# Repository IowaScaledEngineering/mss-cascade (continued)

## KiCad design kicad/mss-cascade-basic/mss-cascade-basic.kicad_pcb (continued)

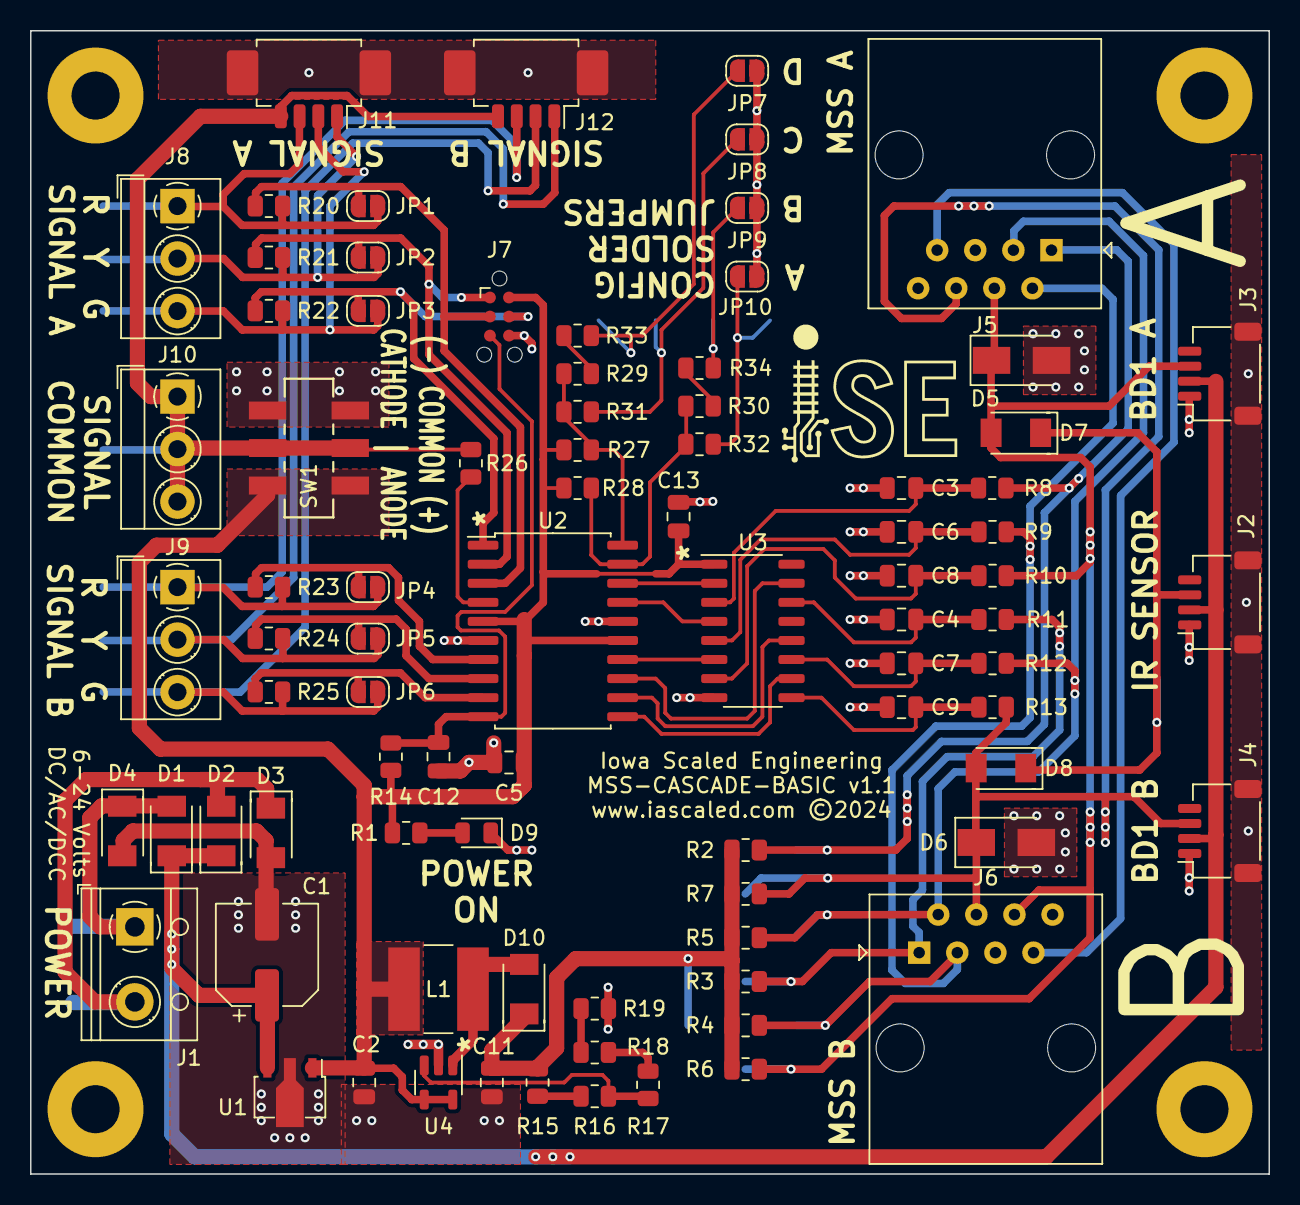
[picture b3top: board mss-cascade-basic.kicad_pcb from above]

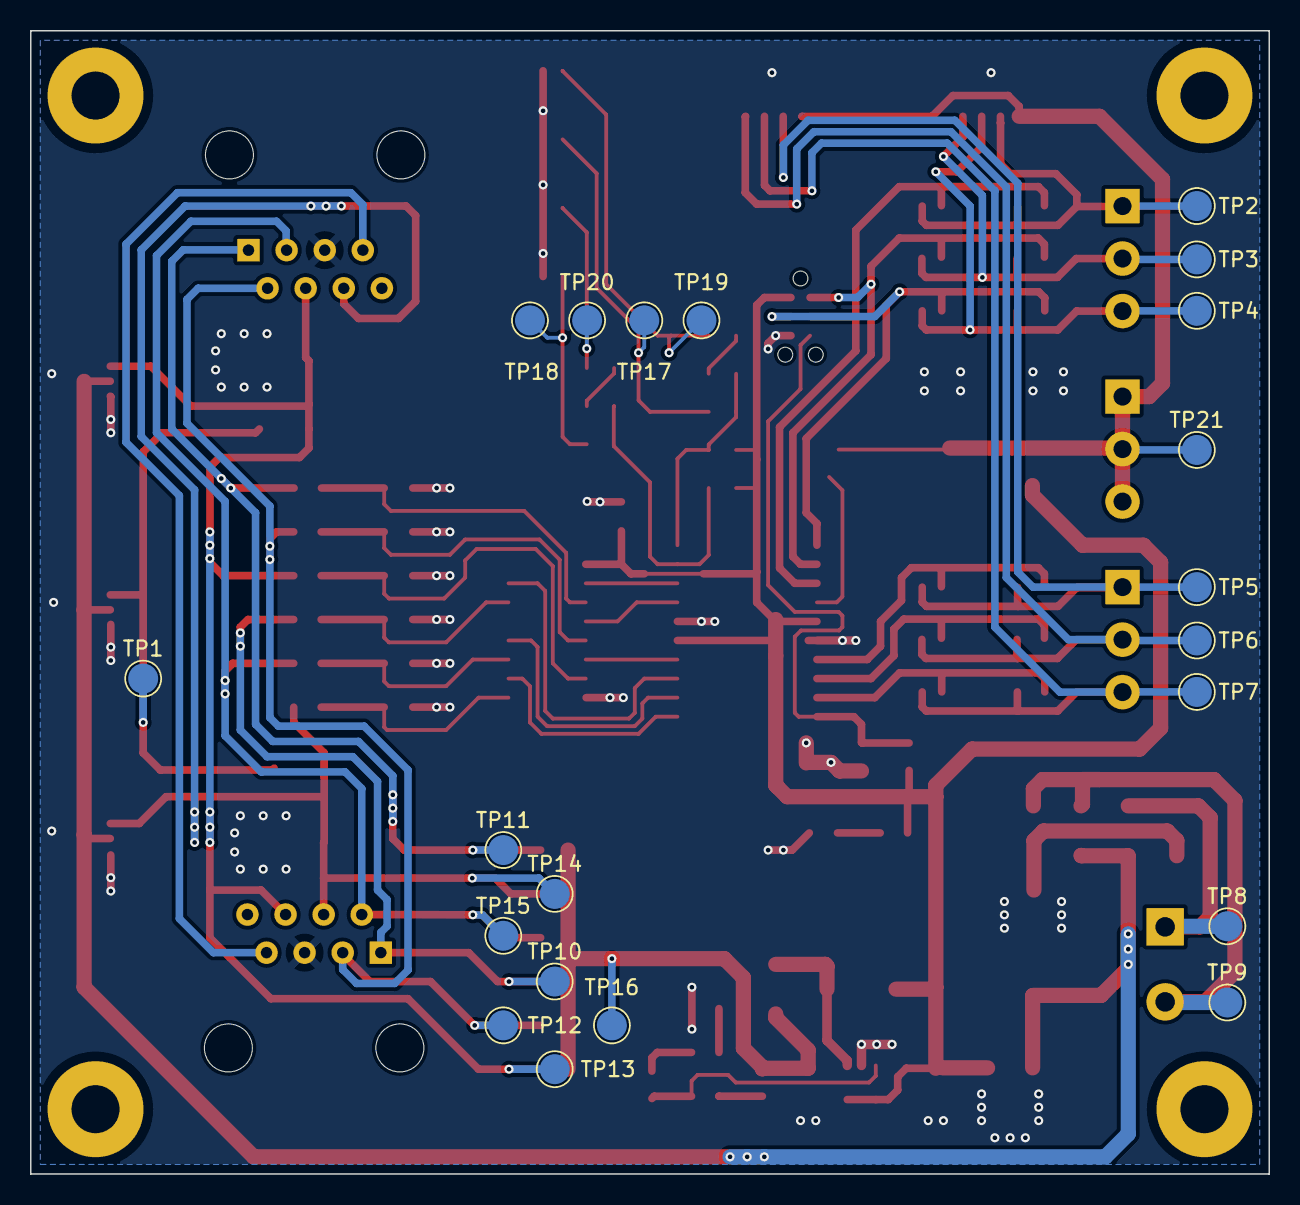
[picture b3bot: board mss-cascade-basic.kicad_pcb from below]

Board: 2 copper layers, 82.6 x 76.2 mm, 109 parts (21 on the bottom side), 55 nets.

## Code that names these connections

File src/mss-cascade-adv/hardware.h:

/*************************************************************************
Title:    Hardware Configuration for MSS-SIDING
Authors:  Michael Petersen <railfan@drgw.net>
          Nathan D. Holmes <maverick@drgw.net>
File:     $Id: $
License:  GNU General Public License v3

LICENSE:
    Copyright (C) 2024 Michael Petersen & Nathan Holmes

    This program is free software; you can redistribute it and/or modify
    it under the terms of the GNU General Public License as published by
    the Free Software Foundation; either version 3 of the License, or
    any later version.

    This program is distributed in the hope that it will be useful,
    but WITHOUT ANY WARRANTY; without even the implied warranty of
    MERCHANTABILITY or FITNESS FOR A PARTICULAR PURPOSE.  See the
    GNU General Public License for more details.

*************************************************************************/

#ifndef _HARDWARE_H_
#define _HARDWARE_H_

#define SWITCH_UPDATE_TIME_MS     25
#define LOOP_UPDATE_TIME_MS       50
#define TURNOUT_LOCKOUT_TIME_MS  200
#define STARTUP_LOCKOUT_TIME_MS  500

#define EEPROM_SIGNAL_AU_BASE  ((uint8_t*)0x00)
#define EEPROM_SIGNAL_AL_BASE  ((uint8_t*)0x08)
#define EEPROM_SIGNAL_BU_BASE  ((uint8_t*)0x10)
#define EEPROM_SIGNAL_BL_BASE  ((uint8_t*)0x18)


#define TCA9555_ADDR_000  0x20
#define TCA9555_ADDR_001  0x21
#define TCA9555_GPIN0        0
#define TCA9555_GPIN1        1
#define TCA9555_GPOUT0       2
#define TCA9555_GPOUT1       3
#define TCA9555_GPDDR0       6
#define TCA9555_GPDDR1       7

// TCA9555 0x20 - GPIO 0
//  IO07 - Input  - Option Switch E
//  IO06 - Input  - Option Switch D
//  IO05 - Input  - Option Switch C
//  IO04 - Input  - Option Switch B
//  IO03 - Input  - Option Switch A
//  IO02 - Input  - /SW3
//  IO01 - Input  - /SW4
//  IO00 - Input  - MSS v2


#define SWITCH_SW3_IN                0x02
#define SWITCH_SW4_IN                0x04


#define OPTION_MSS_V2                0x01
#define OPTION_COMMON_ANODE          0x02  // Reuse this bit in the options byte - normally SW3
#define OPTION_A_APPROACH_LIGHTING   0x08
#define OPTION_B_RESERVED            0x10
#define OPTION_C_SEARCHLIGHT_MODE    0x20
#define OPTION_D_RESERVED            0x40
#define OPTION_E_CONFIG_MODE         0x80


// TCA9555 0x20 - GPIO 1
//  IO17 - Input  - B - AA In
//  IO16 - Input  - B - AD In
//  IO15 - Input  - A - S
//  IO14 - Input  - B - S
//  IO13 - Input  - A - A In
//  IO12 - Input  - A - AA In
//  IO11 - Input  - B - A In
//  IO10 - Input  - A - AD In

#define MSS_B_AA_IN           0x80
#define MSS_B_AD_IN           0x40
#define MSS_A_S               0x20
#define MSS_B_S               0x10
#define MSS_A_A_IN            0x08
#define MSS_A_AA_IN           0x04
#define MSS_B_A_IN            0x02
#define MSS_A_AD_IN           0x01

// TCA9555 0x21 - GPIO 0
//  IO07 - Output - Clear Conf Amber LED
//  IO06 - Output - AD Conf Amber LED
//  IO05 - Output - AD+AA Conf Amber LED
//  IO04 - Output - AA Conf Amber LED
//  IO03 - Output - A Conf Amber LED
//  IO02 - Output - S Conf Amber LED
//  IO01 - Output - Sig B Conf Blue LED
//  IO00 - Output - Sig A Conf Blue LED


#define CONF_LED_SIGNAL_A            0x01
#define CONF_LED_SIGNAL_B            0x02
#define CONF_LED_ASPECT_S            0x04
#define CONF_LED_ASPECT_A            0x08
#define CONF_LED_ASPECT_AA           0x10
#define CONF_LED_ASPECT_AD_AA        0x20
#define CONF_LED_ASPECT_AD           0x40
#define CONF_LED_ASPECT_CLR          0x80


// TCA9555 0x21 - GPIO 1
//  IO17 - Input  - Switch LH
//  IO16 - Input  - Switch UH
//  IO15 - Output - Conf Sig LH Red
//  IO14 - Output - Conf Sig LH Amber
//  IO13 - Output - Conf Sig LH Green
//  IO12 - Output - Conf Sig UH Red
//  IO11 - Output - Conf Sig UH Amber
//  IO10 - Output - Conf Sig UH Green

#define SWITCH_SW6_IN         0x80
#define SWITCH_SW5_IN         0x40
#define CONF_LED_LOWER_RED    0x20
#define CONF_LED_LOWER_YELLOW 0x10
#define CONF_LED_LOWER_GREEN  0x08
#define CONF_LED_UPPER_RED    0x04
#define CONF_LED_UPPER_YELLOW 0x02
#define CONF_LED_UPPER_GREEN  0x01

// Switch masks are actually used for all interaction
//  with the switches, so we don't have to remember
//  their hardware bit positions.  All gets normalized
//  during reading

#define SWITCHMASK_LEFT         0x01
#define SWITCHMASK_RIGHT        0x02
#define SWITCHMASK_UPPER_HEAD   0x04
#define SWITCHMASK_LOWER_HEAD   0x08

// Signal Port Connections
// These are in the order of:
//  Red address, bitmask
//  Yellow address, bitmask
//  Green address, bitmask

#define SIGNAL_HEAD_AU_DEF   &PORTA, _BV(PA7), &PORTA, _BV(PA6), &PORTA, _BV(PA5)
#define SIGNAL_HEAD_AL_DEF   &PORTA, _BV(PA4), &PORTA, _BV(PA3), &PORTB, _BV(PB0)
#define SIGNAL_HEAD_BU_DEF   &PORTB, _BV(PB6), &PORTB, _BV(PB5), &PORTB, _BV(PB4)
#define SIGNAL_HEAD_BL_DEF   &PORTB, _BV(PB3), &PORTB, _BV(PB2), &PORTB, _BV(PB1)

bool getSwitches(uint8_t* retval);
bool getOptions(uint8_t* retval);
bool getMSS(uint8_t* retval, bool mss_v2);
void lampTest();


#endif

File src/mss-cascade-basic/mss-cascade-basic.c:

/*************************************************************************
Title:    MSS-CASCADE-BASIC
Authors:  Michael Petersen <railfan@drgw.net>
          Nathan D. Holmes <maverick@drgw.net>
File:     $Id: $
License:  GNU General Public License v3

LICENSE:
    Copyright (C) 2024 Michael Petersen & Nathan Holmes

    This program is free software; you can redistribute it and/or modify
    it under the terms of the GNU General Public License as published by
    the Free Software Foundation; either version 3 of the License, or
    any later version.

    This program is distributed in the hope that it will be useful,
    but WITHOUT ANY WARRANTY; without even the implied warranty of
    MERCHANTABILITY or FITNESS FOR A PARTICULAR PURPOSE.  See the
    GNU General Public License for more details.

*************************************************************************/

#include <avr/io.h>
#include <avr/interrupt.h>
#include <avr/wdt.h>
#include <util/delay.h>
#include <util/atomic.h>

#include <avr/sleep.h>
#include <stdbool.h>
#include <stdint.h>

#include "debouncer.h"
#include "optionSwitches.h"
#include "signalHead.h"
#include "mss.h"

#define LOOP_UPDATE_TIME_MS       50
#define STARTUP_LOCKOUT_TIME_MS  500

#define MIN(a,b) ((a)<(b)?(a):(b))
#define MAX(a,b) ((a)>(b)?(a):(b))

volatile uint8_t signalHeadOptions = 0;
volatile uint32_t millis = 0;
SignalState_t signalA;
SignalState_t signalB;

// A few hardware definitions

// MSS Port Connections
// These are in the order of:
//  Adjacent address, bitmask
//  Approach address, bitmask
//  Adv Approach address, bitmask
//  Divering Approach address, bitmask

#define MSS_PORT_A_DEF   &PINA, _BV(4), &PINA, _BV(3), &PINA, _BV(2), NULL, _BV(0)
#define MSS_PORT_B_DEF   &PINA, _BV(7), &PINA, _BV(6), &PINA, _BV(5), NULL, _BV(0)

// Signal Port Connections
// These are in the order of:
//  Red address, bitmask
//  Yellow address, bitmask
//  Green address, bitmask

#define SIGNAL_HEAD_A_DEF   &PORTB, _BV(PB2), &PORTB, _BV(PB1), &PORTB, _BV(PB0)
#define SIGNAL_HEAD_B_DEF   &PORTB, _BV(PB4), &PORTB, _BV(PB5), &PORTB, _BV(PB6)


uint32_t getMillis()
{
	uint32_t retmillis;
	ATOMIC_BLOCK(ATOMIC_RESTORESTATE) 
	{
		retmillis = millis;
	}
	return retmillis;
}

ISR(TIMER0_COMPA_vect) 
{
	static uint8_t flasherCounter = 0;
	static uint8_t flasher = 0;
	static uint8_t pwmPhase = 0;
	static uint8_t subMillisCounter = 0;
	
	// The ISR does two main things - updates the LED outputs since
	//  PWM is done through software, and updates millis which is used
	//  to trigger various events
	// We need this to run at roughly 125 Hz * number of PWM levels (32).  That makes a nice round 4kHz
	
	// First thing, output the signals so that the PWM doesn't get too much jitter

	signalHeadISR_OutputPWM(&signalA, signalHeadOptions, pwmPhase, SIGNAL_HEAD_A_DEF);
	signalHeadISR_OutputPWM(&signalB, signalHeadOptions, pwmPhase, SIGNAL_HEAD_B_DEF);

	// Now do all the counter incrementing and such
	if (++subMillisCounter >= 4)
	{
		subMillisCounter = 0;
		millis++;
	}

	pwmPhase = (pwmPhase + 1) & 0x1F;

	if (0 == pwmPhase)
	{
		pwmPhase = 0;
		flasherCounter++;
		if (flasherCounter > 94)
		{
			flasher ^= 0x01;
			flasherCounter = 0;
		}

		// We rolled over the PWM counter, calculate the next PWM widths
		// This runs at 125 frames/second essentially

		signalHeadISR_AspectToNextPWM(&signalA, flasher, signalHeadOptions);
		signalHeadISR_AspectToNextPWM(&signalB, flasher, signalHeadOptions);
	}
}

void initializeTimer()
{
	TIMSK = 0;                                    // Timer interrupts OFF
	// Set up Timer/Counter0 for 100Hz clock
	TCCR0A = 0b00000001;  // CTC Mode
	TCCR0B = 0b00000010;  // CS01 - 1:8 prescaler
	OCR0A = 250;           // 8MHz / 8 / 125 = 8kHz
	TIMSK = _BV(OCIE0A);
}

int main(void)
{
	MSSPort_t mssPortA;
	MSSPort_t mssPortB;
	DebounceState8_t optionsDebouncer;
	uint32_t lastReadTime = 0;
	uint32_t currentTime = 0;
	uint8_t initialLockout = (STARTUP_LOCKOUT_TIME_MS)/(LOOP_UPDATE_TIME_MS);
	uint8_t optionJumpers = 0;
	
	// Deal with watchdog first thing
	MCUSR = 0;              // Clear reset status
	wdt_reset();            // Reset the WDT, just in case it's still enabled over reset
	wdt_enable(WDTO_1S);    // Enable it at a 1S timeout.

	// PORT A
	//  PA7 - Input  - B MSS - Adjacent
	//  PA6 - Input  - B MSS - Approach
	//  PA5 - Input  - B MSS - Advance Approach
	//  PA4 - Input  - A MSS - Adjacent
	//  PA3 - Input  - A MSS - Approach
	//  PA2 - Input  - A MSS - Advance Approach
	//  PA1 - Analog - Options 1
	//  PA0 - Analog - Options 0

	// PORT B
	//  PB7 - n/a    - /RESET (not I/O pin)
	//  PB6 - Output - B Signal - GREEN  (low=active)
	//  PB5 - Output - B Signal - YELLOW (low=active)
	//  PB5 - Output - B Signal - RED (low=active)
	//  PB3 - Input  - Common anode / common cathode sense (1 = common anode)
	//  PB2 - Output - A Signal - GREEN (low=active)
	//  PB1 - Output - A Signal - YELLOW (low=active)
	//  PB0 - Output - A Signal - RED (low=active)

	PORTA = 0b11111100;
	DDRA  = 0b00000000;

	PORTB = 0b11111111;
	DDRB  = 0b01110111;

	initializeTimer();
	initializeOptions(&optionsDebouncer);

	signalHeadInitialize(&signalA);
	signalHeadInitialize(&signalB);

	signalHeadAspectSet(&signalA, ASPECT_OFF);
	signalHeadAspectSet(&signalB, ASPECT_OFF);
	
	mssPortInitialize(&mssPortA);
	mssPortInitialize(&mssPortB);

	// Need to set common anode or common cathode
	// as quickly as possible to prevent an initialization flash
	// initializeOptions() has already gotten the initial state of the CA/CC line
	optionJumpers = getDebouncedState(&optionsDebouncer);
	if (optionJumpers & OPTION_COMMON_ANODE)
		signalHeadOptions |= SIGNAL_OPTION_COMMON_ANODE;
	else 
		signalHeadOptions &= ~SIGNAL_OPTION_COMMON_ANODE;

	sei();
	wdt_reset();


	while(1)
	{
		wdt_reset();

		currentTime = getMillis();

		// Because debouncing and such is built into option reading and the MSS library, only 
		//  run the updates every 10mS or so.

		if (((uint32_t)currentTime - lastReadTime) > LOOP_UPDATE_TIME_MS)
		{
			uint8_t mssOptions = 0;
			
			SignalAspect_t aspect;
			lastReadTime = currentTime;

			readOptions(&optionsDebouncer);
			optionJumpers = getDebouncedState(&optionsDebouncer);
//			optionJumpers |= OPTION_B_FOUR_ASPECT;// | OPTION_COMMON_ANODE | OPTION_C_SEARCHLIGHT_MODE;

			// Convert global option bits to signal head option bits
			if (optionJumpers & OPTION_C_SEARCHLIGHT_MODE)
				signalHeadOptions |= SIGNAL_OPTION_SEARCHLIGHT;
			else 
				signalHeadOptions &= ~SIGNAL_OPTION_SEARCHLIGHT;

			if (optionJumpers & OPTION_COMMON_ANODE)
				signalHeadOptions |= SIGNAL_OPTION_COMMON_ANODE;
			else 
				signalHeadOptions &= ~SIGNAL_OPTION_COMMON_ANODE;

			// Convert global option bits to MSS option bits
			if (optionJumpers & OPTION_A_APPROACH_LIGHTING)
				mssOptions |= MSS_ASPECT_OPTION_APPRCH_LIGHTING;

			if (optionJumpers & OPTION_B_FOUR_ASPECT)
				mssOptions |= MSS_ASPECT_OPTION_FOUR_INDICATION;


			// Read state of MSS bus ports coming in
			mssReadPort(&mssPortA, MSS_PORT_A_DEF);
			mssReadPort(&mssPortB, MSS_PORT_B_DEF);


			// The purpose of the initialLockout is to give the MSS lines and debouncers time to stabilize before we bring the signals up
			// It just looks cleaner to the user than the signals bouncing all over the place as the lines settle.
			if (0 != initialLockout)
			{
				initialLockout--;
				continue;
			}

			mssIndicationToSingleHeadAspect(mssPortA.indication, &aspect, mssOptions, mssPortApproach(&mssPortB));
			signalHeadAspectSet(&signalB, aspect);
			
			mssIndicationToSingleHeadAspect(mssPortB.indication, &aspect, mssOptions, mssPortApproach(&mssPortA));
			signalHeadAspectSet(&signalA, aspect);
		}

	}
}

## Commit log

2015-10-14 Initial work on Free-mo Modular Signal System integrated cascade board
2015-10-14 Add licensing and update gitignore
2015-10-14 Update description text on schematic
2015-11-09 Upgrade to atmega165a and put in new bus sensing section with 74hc4049
2015-11-24 Cascade, simplified. Removed giant AVR, replaced with attiny48 and some i2c I/O
2015-11-24 Putting it back to the mega165a and fixing all the refdes
2015-11-25 Change refdes on optical occupancy indicator led
2015-11-29 Now goes through gsch2pcb relatively cleanly
2015-11-29 Forgot to add the header symbol for the pin 5-7 jumper
2015-11-29 Minor pinout and footprint adjustments
2015-11-30 Changes needed to make the PCB work - mostly pin changes
2015-11-30 Add more plane
2015-12-01 Misc changes, add LEDs to 3.3 and 12V rails, etc.
2015-12-03 Move U9 further from the switches and add pin 1 markers to the SOs
2015-12-03 Add 1.0 pg
2015-12-31 Add initial framework for development
2016-01-01 Incremental work towards bringing up the MSS board
2016-01-01 Update gitignore to include more stuff I dont' want to see
2016-01-01 Make the IRSENSE head actually function
2016-01-02 More changes. initial support for 3-wire R/G LEDs.
2016-01-02 Add 2 wire RG LED support Implement suppression of blinkies
2016-01-27 Start of cascade module manual
2016-01-28 Convert aspects to a convenient array
2016-05-16 Updates to add configuration tables
2016-06-07 Change 12V rail to a boost converter
2016-06-09 More manual updates
2016-06-24 Fix various logic issues
2016-06-24 Fix avrdude conf for the 165a
2016-06-24 Fix 2-lead R/G LED drives on A1, A2, and B2 channels
2016-06-24 Fix up refdes issues with new regulator
2016-06-24 Changes to add a switching regulator to provide +12V for the MSS bus
2016-06-24 Refactoring a few more things out of main
2016-06-24 Factor out codeline->aspect configuration
2016-09-06 Changes to add wiring diagrams to manual and correct typos
2016-09-06 Update wiring image
2016-09-14 Add provision for MSS standard possibly reversing the logic on the diverging approach line
2016-09-14 Just additional cleanup of the pcb
2016-09-14 Change out input protection circuit for a new one
2016-09-14 Fix copyright date
2016-09-17 Add cascade v1.1
2016-09-27 Revisions to manual per Michael
2017-09-12 Repaginated
2017-09-12 Bag tops
2017-09-12 Fixed minimum supply on page 3. Added new ISE logo.
2024-05-14 Draft version of an mss-cascade-basic
2024-05-23 Schematic updates and moving things around on the basic
2024-06-03 Initial PCB layout for basic cascade
2024-06-03 Add 3d models to footprints
2024-06-09 Add test point for 12V, move connectors to align
2024-07-09 Sent to fab July 2024
2024-07-09 Some fixes
2024-07-15 Move old cascade to mss-cascade-v1 subdirectory
2024-07-16 Start of cascade basic firmware
2024-07-16 More updates
2024-07-23 Initial workingish code
2024-07-25 Add searchlight code to do proper roundel change emulation
2024-07-25 Improve fade in / fade out times
2024-07-25 Factor out the searchlight PWM values and make them defined with macros rather than magic values from my spreadsheet
2024-08-19 Preliminary addition of Atlas signal connectors and the ability to set common anode or cathode
2024-08-19 A few cleanup things
2024-08-26 Change text, add test point for common
2024-08-26 Add cascade basic pg 1.1
2024-09-16 Refactor signal and mss logic for modularity and fix a bunch of bugs
2024-09-16 Fix some issues with option switches
2024-10-14 Make startup a bit cleaner so there's no initialization flash
2024-11-10 Add start of mss-cascade-pro based off the mss-switch
2024-11-26 Continued work on cascade pro
2024-12-04 Initial cut of the cascade pro idea
2024-12-06 PCB Cleanup
2024-12-06 Rename cascade pro to cascade advanced
2024-12-20 Add initial template for advanced source code
2024-12-23 Initial cut with basic functionality
2024-12-24 Initial working version. Code itself is still a mess, but it works correctly now
2024-12-26 A little cleanup on the cascade advanced
2025-01-05 Add 3d models for RJ45s
2025-01-19 Harmonize the signal aspect enum with the cascade advanced
2025-01-19 Make approach lighting only the adjacent block, not also approach blocks
2025-02-18 First whack at a cascade basic test jig
2025-02-23 Fix issues with wire naming
2025-07-20 Change to make "stop" actually "restricting"
2025-08-12 PG for the advanced
2025-09-10 Add manual test procedure
